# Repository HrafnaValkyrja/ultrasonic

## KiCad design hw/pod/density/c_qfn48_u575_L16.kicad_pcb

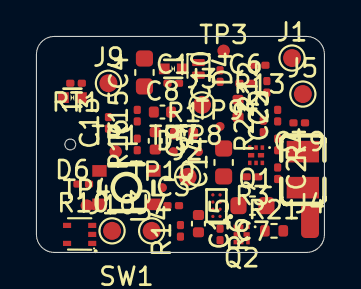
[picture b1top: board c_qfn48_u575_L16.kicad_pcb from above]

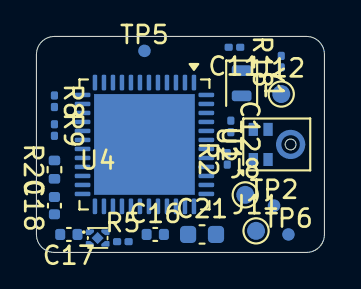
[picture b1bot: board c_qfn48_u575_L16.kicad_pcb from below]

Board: 4 copper layers, 16.0 x 12.0 mm, 74 parts (22 on the bottom side), 42 nets, no tracks yet.

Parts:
C1, C2, C3, C6, C10, C11, C12, C13, C19, C22: C_0201_0603Metric
C4, C7, C14, C21: C_0603_1608Metric
C5, C8, C9, C15, C16, C17, C18: C_0402_1005Metric
D4: D_SOD-882
D5, D6: X1SON-2_L1.0-W0.6-P0.65-BI-1
J1, J2, J3, J5, J7, J8, J9, J10, J11, J12: TestPoint_Pad_D1.0mm
J4: WirePad_1.0x2.0mm
L1: L0806
Q1, Q2: Nexperia_SOT1216_DFN1010B-6
R1, R20, R21: R_0402_1005Metric
R2, R3, R4, R5, R6, R8, R9, R10, R12, R13, R14, R15, R16, R18, R22: R_0201_0603Metric
RT1: R_0201_0603Metric
SW1: SW-SMD_4P-L3.0-W2.6-P1.85-LS3.4
TP1, TP2, TP3, TP4, TP5, TP6: TestPoint_Pad_D0.7mm
TP7, TP8, TP9, TP10: TestDot_D0.5mm
U1: QFN-48-1EP_7x7mm_P0.5mm_EP5.6x5.6mm
U2: Knowles_LGA-5_3.5x2.65mm; Knowles_LGA-5_3.5x2.65mm_Port0.6
U3: DSBGA-8_L1.6-W0.9-R2-C4-P0.40-BL
U4: X2SON-4_L1.0-W1.0-P0.65-TL-EP
U6: SOT-553-5_L1.6-W1.2-P0.50-LS1.6-TL-1
Y1: Crystal_SMD_2012-2Pin_2.0x1.2mm

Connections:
+3V0: C1.1, C2.1, C3.1, C4.1, C5.1, C6.1, C7.1, C14.1, Q1.4, Q2.4, R3.2, R5.2, R15.2, R16.2, R20.2, SW1.1, SW1.2, TP4.1, U1.1, U1.9, U1.21, U1.25, U1.36, U1.48
BRIDGE_RTN: Q1.1, Q2.1, R21.1, R22.1
BTN: R10.1, SW1.3, SW1.4, U1.10
CC: D6.1, J12.1, R18.1
CHG_INT: U1.38, U3.A1
DBG_TX: TP7.1, U1.42
DOCK_VBUS: D4.2, D5.1, J3.1
GA_N: Q1.2, R4.1, U1.17
GA_P: Q1.5, R3.1, U1.29
GB_N: Q2.2, R6.1, U1.28
GB_P: Q2.5, R5.1, U1.31
GND: C1.2, C2.2, C3.2, C4.2, C5.2, C6.2, C7.2, C8.2, C9.2, C10.2, C11.2, C12.2, C13.2, C14.2, C15.2, C16.2, C17.2, C18.2, C19.2, C21.2, C22.2, D5.2, D6.2, J4.1, R1.2, R4.2, R6.2, R9.2, R10.2, R13.2, R18.2, R21.2, RT1.2, TP5.1, U1.8, U1.22, U1.24, U1.35, U1.41, U1.47, U1.49, U2.2, U2.3, U3.D2, U4.2, U4.5, U6.4
I2C_SCL: R15.1, U1.26, U3.B1
I2C_SDA: R16.1, U1.27, U3.C1
I_SENSE: C22.1, R22.2, U1.16
LDO_OUT: C18.1, R20.1, U4.1
LED_A: J7.1, R14.2
LED_K: J8.1, U1.43
LSE_IN: C11.1, U1.3, Y1.1
LSE_OUT: C12.1, U1.4, Y1.2
MDF_CCK: TP8.1, U1.45
MDF_SDI: TP9.1, U1.19
MIC_CLK: R2.2, U2.4
MIC_DATA: TP10.1, U1.40, U2.1
MIC_VDD: C13.1, U1.15, U2.5
unnamed: R1.1, U1.44
unnamed: R2.1, U1.39
NRST: C10.1, TP3.1, U1.7
OUT_A: J1.1, Q1.3, Q1.6, Q1.7, Q1.8
OUT_B: J2.1, Q2.3, Q2.6, Q2.7, Q2.8
SWCLK: TP2.1, U1.37
SWDIO: TP1.1, U1.34
TS: J9.1, RT1.1, U1.12, U3.D1
USB_DM: J11.1, U1.32, U6.5
USB_DP: J10.1, U1.33, U6.3
VBAT: C16.1, J5.1, R8.1, U3.C2
VBAT_SENSE: C19.1, R8.2, R9.1, U1.14
VBUS: C15.1, D4.1, R12.1, U3.A2
VBUS_SENSE: R12.2, R13.1, U1.11
VDD11: C8.1, C9.1, L1.2, U1.23, U1.46
VLXSMPS: L1.1, U1.20
VSYS: C17.1, C21.1, R14.1, TP6.1, U3.B2, U4.3, U4.4

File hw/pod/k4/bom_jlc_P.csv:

Comment,Designator,Footprint,LCSC Part #,Qty,In sourcing lock
22u,C14,C_0603_1608Metric,C59461,1,yes
4u7 25V,C15,C_0402_1005Metric,C2858031,1,yes
4u7,C16,C_0402_1005Metric,C23733,1,yes
1u,"C17,C18",C_0402_1005Metric,C52923,2,yes
10u,C21,C_0603_1608Metric,C19702,1,yes
10n,C22,C_0201_0603Metric,C85930,1,yes
PMEG3005EL,D4,D_SOD-882,C282565,1,yes
TPD1E10B06DPYR,D5,X1SON-2_L1.0-W0.6-P0.65-BI-1,C48260,1,yes
BM28B0.6-30DP/2-0.35V(51),J21,BM28B0.6-30DP_2-0.35V,C424570,1,dated lookup
2u2,L1,L0806,C337891,1,yes
PMCXB290UE,"Q1,Q2",Nexperia_SOT1216_DFN1010B-6,C19654206,2,yes
2k2,"R10,R14",R_0201_0603Metric,C473508,2,yes
0,R20,R_0402_1005Metric,C17168,1,yes
0.1,R21,R_0402_1005Metric,C409058,1,yes
1k,R22,R_0201_0603Metric,C270365,1,yes
1M,"R23,R8,R9",R_0201_0603Metric,C473482,3,yes
100k,"R12,R13,R3,R4,R5,R6",R_0201_0603Metric,C270364,6,yes
10k B3435,RT1,R_0201_0603Metric,C98098,1,yes
KMT022NGJLHS,SW1,SW-SMD_4P-L3.0-W2.6-P1.85-LS3.4,C221707,1,yes
BQ25180YBGR,U3,DSBGA-8_L1.6-W0.9-R2-C4-P0.40-BL,C3682423,1,yes
TPS7A2030PDQNR,U4,X2SON-4_L1.0-W1.0-P0.65-TL-EP,C5220164,1,yes
TPD2E2U06DRLR,U6,SOT-553-5_L1.6-W1.2-P0.50-LS1.6-TL-1,C1972959,1,yes
